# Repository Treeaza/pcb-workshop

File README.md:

# pcb workshop
 
 ## Copyright 2023, Jasper Rubin. All rights reserved.
 
KiCAD files for my PCB design workshop at MUN's Student Design Hub. The files contained in this repository are for demonstration purposes, and have no gurantee of functionality.

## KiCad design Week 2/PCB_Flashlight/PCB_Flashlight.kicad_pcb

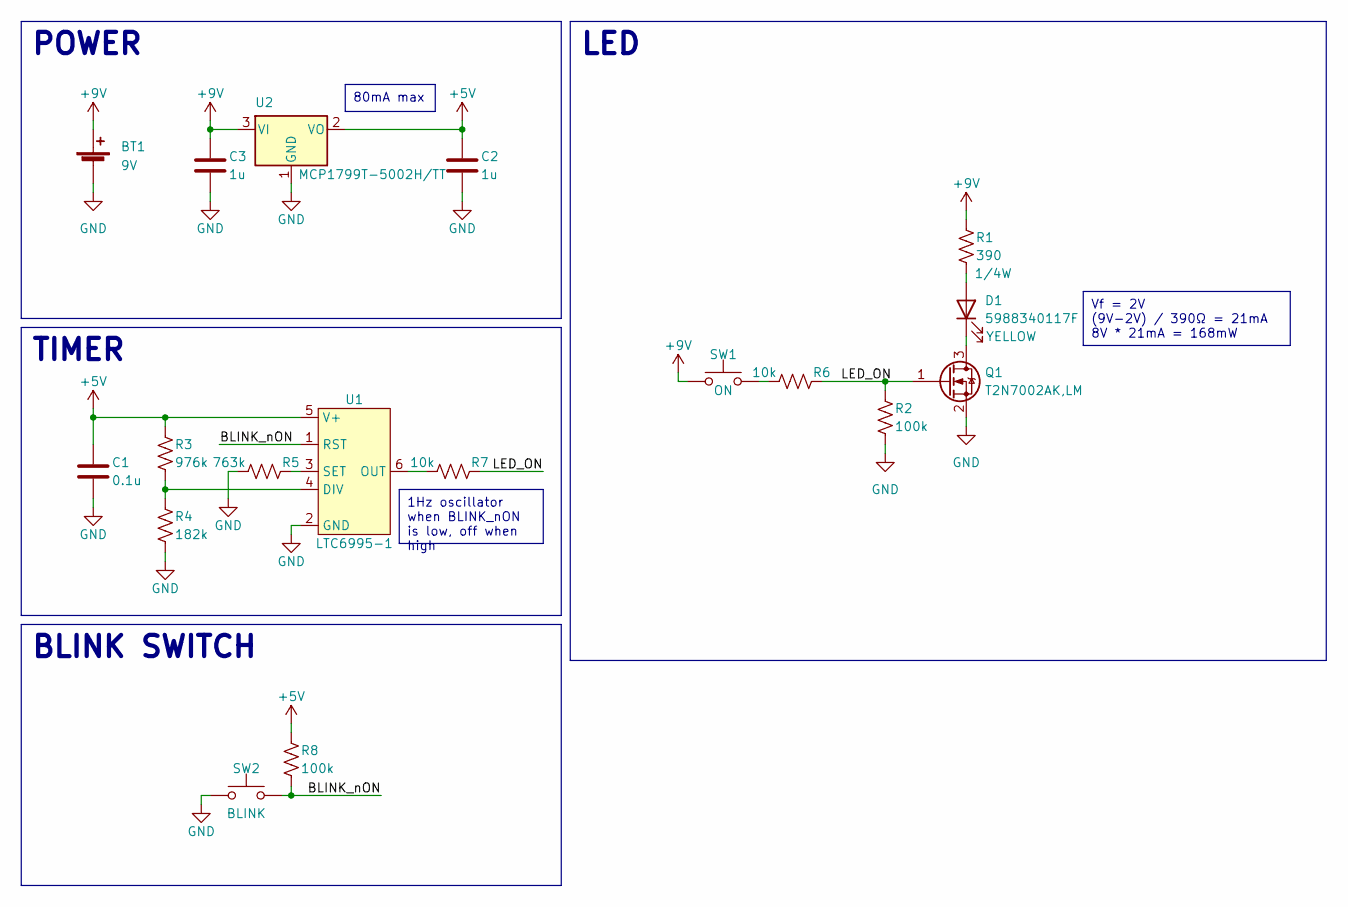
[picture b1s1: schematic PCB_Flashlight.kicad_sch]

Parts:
BT1: 9V; PinHeader_1x02_P2.54mm_Vertical
C1: 0.1u; C_0805_2012Metric_Pad1.18x1.45mm_HandSolder
C2, C3: 1u; C_0805_2012Metric_Pad1.18x1.45mm_HandSolder
D1: 5988340117F
Q1: T2N7002AK,LM; SOT-23_Handsoldering
R1: 390; R_0805_2012Metric_Pad1.20x1.40mm_HandSolder
R2, R8: 100k; R_0805_2012Metric_Pad1.20x1.40mm_HandSolder
R3: 976k; R_0805_2012Metric_Pad1.20x1.40mm_HandSolder
R4: 182k; R_0805_2012Metric_Pad1.20x1.40mm_HandSolder
R5: 763k; R_0805_2012Metric_Pad1.20x1.40mm_HandSolder
R6, R7: 10k; R_0805_2012Metric_Pad1.20x1.40mm_HandSolder
SW1: ON; SW_PUSH_6mm
SW2: BLINK; SW_PUSH_6mm
U1: LTC6995-1; SOT-23-6_Handsoldering
U2: MCP1799T-5002H/TT; SOT-23

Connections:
+5V: C1.1, C2.1, R3.1, R8.1, U1.5 (V+), U2.2 (VO)
+9V: BT1.1 (+), C3.1, R1.1, SW1.1, U2.3 (VI)
/BLINK_nON: R8.2, SW2.2, U1.1 (RST)
/LED_ON: Q1.1 (G), R2.1, R6.2, R7.2
GND: BT1.2 (-), C1.2, C2.2, C3.2, Q1.2 (S), R2.2, R4.2, R5.1, SW2.1, U1.2 (GND), U2.1 (GND)
unnamed: D1.2 (A), R1.2
unnamed: D1.1 (K), Q1.3 (D)
unnamed: R6.1, SW1.2
unnamed: R3.2, R4.1, U1.4 (DIV)
unnamed: R7.1, U1.6 (OUT)
unnamed: R5.2, U1.3 (SET)

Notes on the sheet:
1Hz oscillator when BLINK_nON is low, off when high
80mA max
Vf = 2V (9V-2V) / 390Ω = 21mA 8V * 21mA = 168mW
TIMER
POWER
BLINK SWITCH
LED

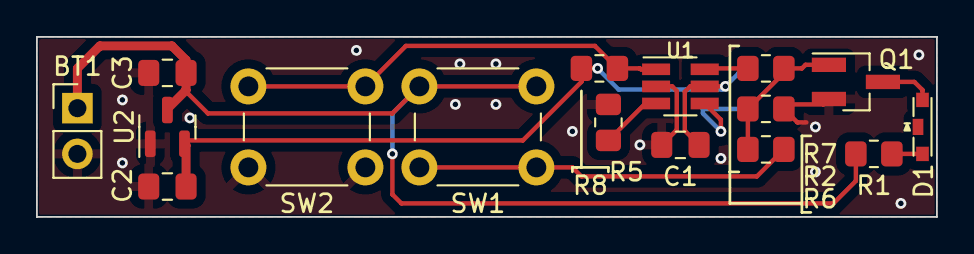
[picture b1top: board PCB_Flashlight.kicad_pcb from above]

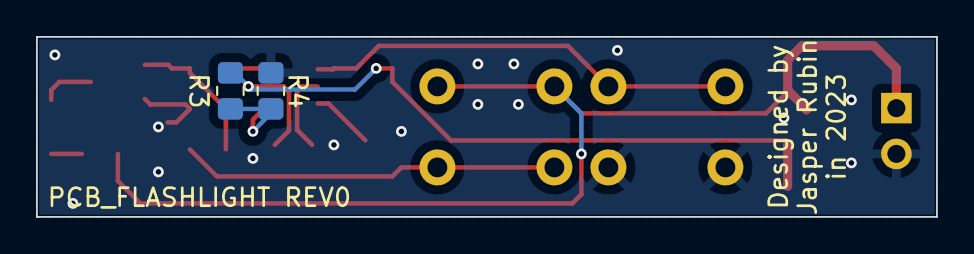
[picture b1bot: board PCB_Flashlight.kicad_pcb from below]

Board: 2 copper layers, 50.0 x 10.0 mm, 18 parts (2 on the bottom side), 11 nets.

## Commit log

2023-10-09 Rearrange, make workshop 2 content
2023-10-10 Make the routing less horrendous
